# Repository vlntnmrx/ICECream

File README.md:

# ICECream
FPGA Devboard for the ICE405K made with audio in mind
## State
Abandoned...

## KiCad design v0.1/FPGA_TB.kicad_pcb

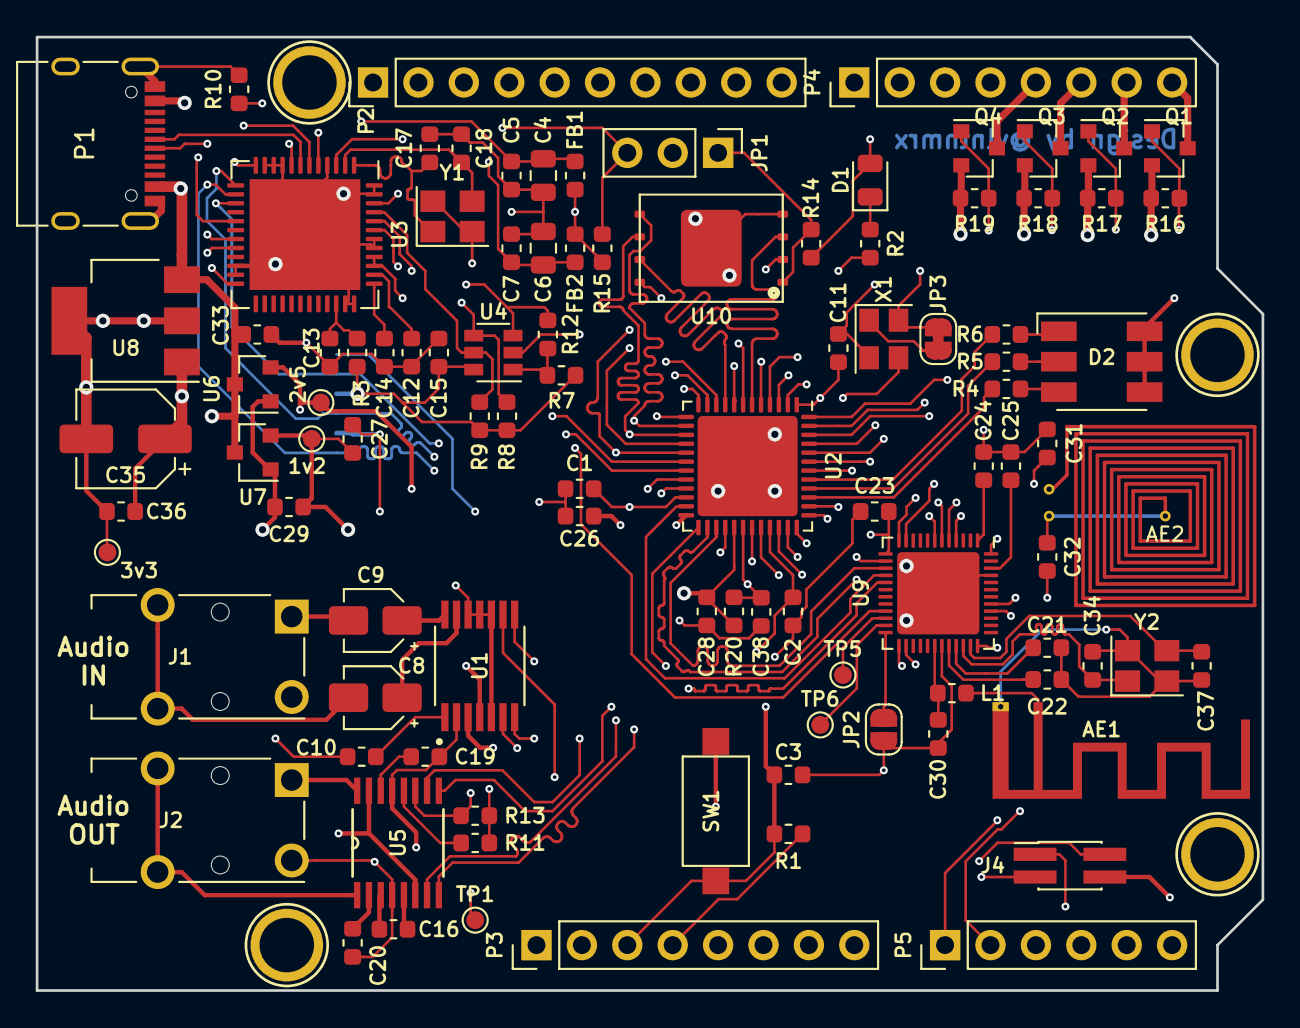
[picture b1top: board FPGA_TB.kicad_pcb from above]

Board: 4 copper layers, 68.6 x 53.3 mm, 105 parts (1 on the bottom side), 107 nets.

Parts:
1v2, 2v5, 3v3: TestPoint; TestPoint_Pad_D1.0mm
AE1: Antenna; Texas_SWRA117D_2.4GHz_Left
AE2: Antenna_Loop; NFC_Antenna_small
C1, C2, C3, C5, C7, C10, C11, C15: 0,1uF; C_0603_1608Metric
C4, C6: 4.7uF; C_0805_2012Metric
C8, C9: 1uF; CP_Elec_3x5.4
C12, C14, C26: 0.1uF; C_0603_1608Metric
C13: 10nF; C_0603_1608Metric
C16, C20, C25, C29, C33: 1uF; C_0603_1608Metric
C17, C18: 27p; C_0603_1608Metric
C19: 2,2uF; C_0603_1608Metric
C21: 100pF; C_0603_1608Metric
C22: N.C.; C_0603_1608Metric
C23: 0.1nF; C_0603_1608Metric
C24, C27, C28, C36, C38: 100nF; C_0603_1608Metric
C30: 0.8pF; C_0603_1608Metric
C31, C32: 470pF; C_0603_1608Metric
C34, C37: 12pF; C_0603_1608Metric
C35: 4.7uF; CP_Elec_5x5.8
D1: LED; LED_0805_2012Metric
D2: LED_RGB; LED_RGB_5050-6
FB1, FB2: 600R; L_0603_1608Metric
J1, J2: AudioJack3; Jack_3.5mm_Switronic_ST-005-G_horizontal
J3: Micro_SD_Card_Det_Hirose_DM3AT; microSD_HC_Hirose_DM3AT-SF-PEJM5
J4: Conn_01x04; PinHeader_2x02_P1.27mm_Vertical_SMD
JP1: Jumper_NC_Dual; PinHeader_1x03_P2.54mm_Vertical
JP2: Jumper_NO_Small; SolderJumper-2_P1.3mm_Open_RoundedPad1.0x1.5mm
JP3: Jumper_NC_Small; SolderJumper-2_P1.3mm_Bridged_RoundedPad1.0x1.5mm
L1: 3.9nH; L_0603_1608Metric
P1: USB_C_Plug_USB2.0; USB_C_Receptacle_XKB_U262-16XN-4BVC11
P2: Digital; PinHeader_1x10_P2.54mm_Vertical
P3: Power; PinHeader_1x08_P2.54mm_Vertical
P4: Digital; PinHeader_1x08_P2.54mm_Vertical
P5: Analog; PinHeader_1x06_P2.54mm_Vertical
P5#2, P6, P7, P8: CONN_01X01; Arduino_1pin
Q1, Q2, Q3, Q4: IRLML2060; SOT-23
R1, R3, R7, R8, R9, R11, R13, R14, R15, R16, R17, R18, R19: 10k; R_0603_1608Metric
R2, R4, R5, R6: 330; R_0603_1608Metric
R10: 12k 1%; R_0603_1608Metric
R12: 2k; R_0603_1608Metric
R20: 100; R_0603_1608Metric
SW1: SW_Push; SW_SPST_CK_RS282G05A3
TP1, TP5, TP6: TestPoint; TestPoint_Pad_D1.0mm
U1: PCM1808PWG4; SOP65P640X120-14N
U2: ICE40UP5K-SG48ITR; QFN-48-1EP_7x7mm_P0.5mm_EP5.6x5.6mm
U3: FT232H; QFN-48-1EP_8x8mm_P0.5mm_EP6.2x6.2mm
U4: 93LCxxAxxOT; SOT-23-6
U5: WM8524CGEDT; SOP65P640X110-16N
U6: AP2127N-2.5; SOT-23
U7: APE8865N-12-HF-3; SOT-23
U8: AMS1117-3.3; SOT-223-3_TabPin2
U9: nRF52832-QFxx; QFN-48-1EP_6x6mm_P0.4mm_EP4.6x4.6mm
U10: W25Q32JVZP; WSON-8_8x6_P1.27mm
X1: ASE-xxxMHz; Oscillator_SMD_Abracon_ASE-4Pin_3.2x2.5mm
Y1: 12MHz; Crystal_SMD_3225-4Pin_3.2x2.5mm
Y2: 32MHz; Crystal_SMD_3225-4Pin_3.2x2.5mm

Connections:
+1V2: 1v2.1, C27.1, C28.1, C29.2, R20.2, U2.29, U7.2
+2V5: 2v5.1, C26.2, P3.1, U2.24, U6.2
+3V3: 3v3.1, C1.2, C2.2, C11.2, C15.1, C23.2, C35.2, C36.1, D1.2, D2.4, D2.5, D2.6, FB1.2, FB2.2, J3.4, J4.4, JP3.2, P3.2, P3.4, R1.1, R3.1, R7.1, R8.1, R9.1, R11.1, R13.1, R14.1, R15.2, U1.4, U2.1, U2.22, U2.33, U3.12, U3.24, U3.39, U3.40, U3.46, U4.6, U5.6, U5.15, U8.2, U9.13, U9.36, U9.48, U10.8, X1.4
+5V: C33.1, P1.A4, P1.A9, P1.B4, P1.B9, P3.5, P3.8, U1.3, U6.3, U7.3, U8.3
/ADC_BCK: U1.8, U2.36
/ADC_DOUT: U1.9, U2.43
/ADC_LRCK: U1.7, U2.38
/ADC_SCKI: U1.6, U2.42
/DAC_BCLK: U2.31, U5.9
/DAC_DACDAT: U2.32, U5.7
/DAC_LRCLK: U2.34, U5.8
/DAC_MCLK: U2.37, U5.10
/FET0: Q1.1, R16.1, U2.46
/FET1: Q2.1, R17.1, U2.47
/FET2: Q3.1, R18.1, U2.44
/FET3: Q4.1, R19.1, U2.48
/FLASH_CLK: J3.5, U2.15, U3.13, U10.6
/FLASH_CS: JP1.1, R14.2, U10.1
/FLASH_IO2: U2.6, U10.3
/FLASH_IO3: U2.9, U10.7
/FLASH_MISO: J3.7, U2.17, U3.14, U10.2
/FLASH_MOSI: J3.3, U2.14, U3.15, U10.5
/FPGA_DONE: R2.2, U2.7, U3.19
/FPGA_NRF0: U2.26, U9.14
/FPGA_NRF1: U2.27, U9.15
/FPGA_NRF2: U2.23, U9.16
/FPGA_NRF3: U2.25, U9.17
/FPGA_SD_SS: J3.2, U2.28
/FPGA_reset: C3.1, P3.3, R1.2, SW1.2, U2.8, U3.20
/FTDI_CS: JP1.3, R15.1, U3.17
/NRF_SWDCLK: J4.3, U9.25
/NRF_SWDIO: J4.2, U9.26
/NRF_reset: JP2.2, U9.24
/PINH_A0: P5.6, U9.4
/PINH_A1: P5.5, U9.5
/PINH_A2: P5.4, U9.6
/PINH_A3: P5.3, U9.7
/PINH_A4: P5.2, U9.40
/PINH_A5: P5.1, U9.41
/PINH_D0: P4.8, Q1.3
/PINH_D1: P4.7, Q2.3
/PINH_D2: P4.6, Q3.3
/PINH_D3: P4.5, Q4.3
/PINH_D4: P4.4, U2.45
/PINH_D5: P4.3, U2.2
/PINH_D6: P4.2, U2.4
/PINH_D7: P4.1, U2.3
/PINH_D8: P2.10, U2.10
/PINH_D9: P2.9, U2.11
/PINH_D10: P2.8, U2.12
/PINH_D11: P2.7, U2.21
/PINH_D12: P2.6, U2.13
/PINH_D13: P2.5, U2.20
/PINH_D14: P2.2, U2.19
/PINH_D15: P2.1, U2.18
/PINH_SWO: P2.3, U9.21
/RF_ANT: C30.1, L1.1, U9.30
/SPI_FPGA_SS: JP1.2, U2.16
/USB_N: P1.A7, U3.6
/USB_P: P1.A6, U3.7
GND: AE1.2, C1.1, C2.1, C3.2, C4.2, C5.2, C6.2, C7.2, C10.2, C11.1, C12.2, C13.2, C14.2, C15.2, C17.2, C18.2, C19.2, C20.2, C21.2, C22.2, C23.1, C24.2, C25.1, C26.1, C27.2, C28.2, C29.1, C30.2, C31.2, C32.2, C33.2, C34.2, C35.1, C36.2, C37.2, C38.1, J1.S, J2.S, J3.6, J3.11, J4.1, JP2.1, P1.A1, P1.A12, P1.B1, P1.B12, P1.S1, P2.4, P3.6, P3.7, Q1.2, Q2.2, Q3.2, Q4.2, R10.2, R16.2, R17.2, R18.2, R19.2, SW1.1, U1.2, U1.5, U1.10, U1.11, U1.12, U2.49, U3.4, U3.9, U3.10, U3.11, U3.22, U3.23, U3.35, U3.36, U3.41, U3.42, U3.47, U3.48, U3.49, U4.2, U5.4, U5.13, U6.1, U7.1, U8.1, U9.31, U9.45, U9.49, U10.4, U10.9, X1.2, Y1.2, Y1.4, Y2.2, Y2.4
unnamed: AE1.1, L1.2
unnamed: AE2.1, C31.1, U9.11
unnamed: AE2.2, C32.1, U9.12
unnamed: C4.1, C5.1, FB1.1, U3.8
unnamed: C6.1, C7.1, FB2.1, U3.3
unnamed: C8.1, U1.13
unnamed: C8.2, J1.T
unnamed: C9.1, U1.14
unnamed: C9.2, J1.R
unnamed: C10.1, U1.1
unnamed: C12.1, U3.38
unnamed: C13.1, R3.2, U3.34
unnamed: C14.1, U3.37
unnamed: C16.1, U5.3
unnamed: C16.2, U5.5
unnamed: C17.1, U3.1, Y1.1
unnamed: C18.1, U3.2, Y1.3
unnamed: C19.1, U5.14
unnamed: C20.1, U5.2
unnamed: C21.1, U9.33
unnamed: C22.1, U9.32
unnamed: C24.1, U9.1
unnamed: C25.2, U9.46
unnamed: C34.1, U9.34, Y2.1
unnamed: C37.1, U9.35, Y2.3
unnamed: C38.2, R20.1, U2.5, U2.30
unnamed: D1.1, R2.1
unnamed: D2.1, R6.2
unnamed: D2.2, R5.2
unnamed: D2.3, R4.2
unnamed: J2.R, U5.16
unnamed: J2.T, U5.1
unnamed: JP3.1, X1.1
unnamed: R4.1, U2.39
unnamed: R5.1, U2.40
unnamed: R6.1, U2.41
unnamed: R8.2, U3.44, U4.4
unnamed: R9.2, U3.45, U4.5
unnamed: R10.1, U3.5
unnamed: R11.2, U5.12
unnamed: R12.1, U3.43, U4.3
unnamed: R7.2, R12.2, U4.1
unnamed: R13.2, TP1.1, U5.11
unnamed: TP5.1, U9.22
unnamed: TP6.1, U9.23
unnamed: U2.35, X1.3

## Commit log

2020-08-26 Create LICENSE
2020-08-29 Matched some trace lenths
